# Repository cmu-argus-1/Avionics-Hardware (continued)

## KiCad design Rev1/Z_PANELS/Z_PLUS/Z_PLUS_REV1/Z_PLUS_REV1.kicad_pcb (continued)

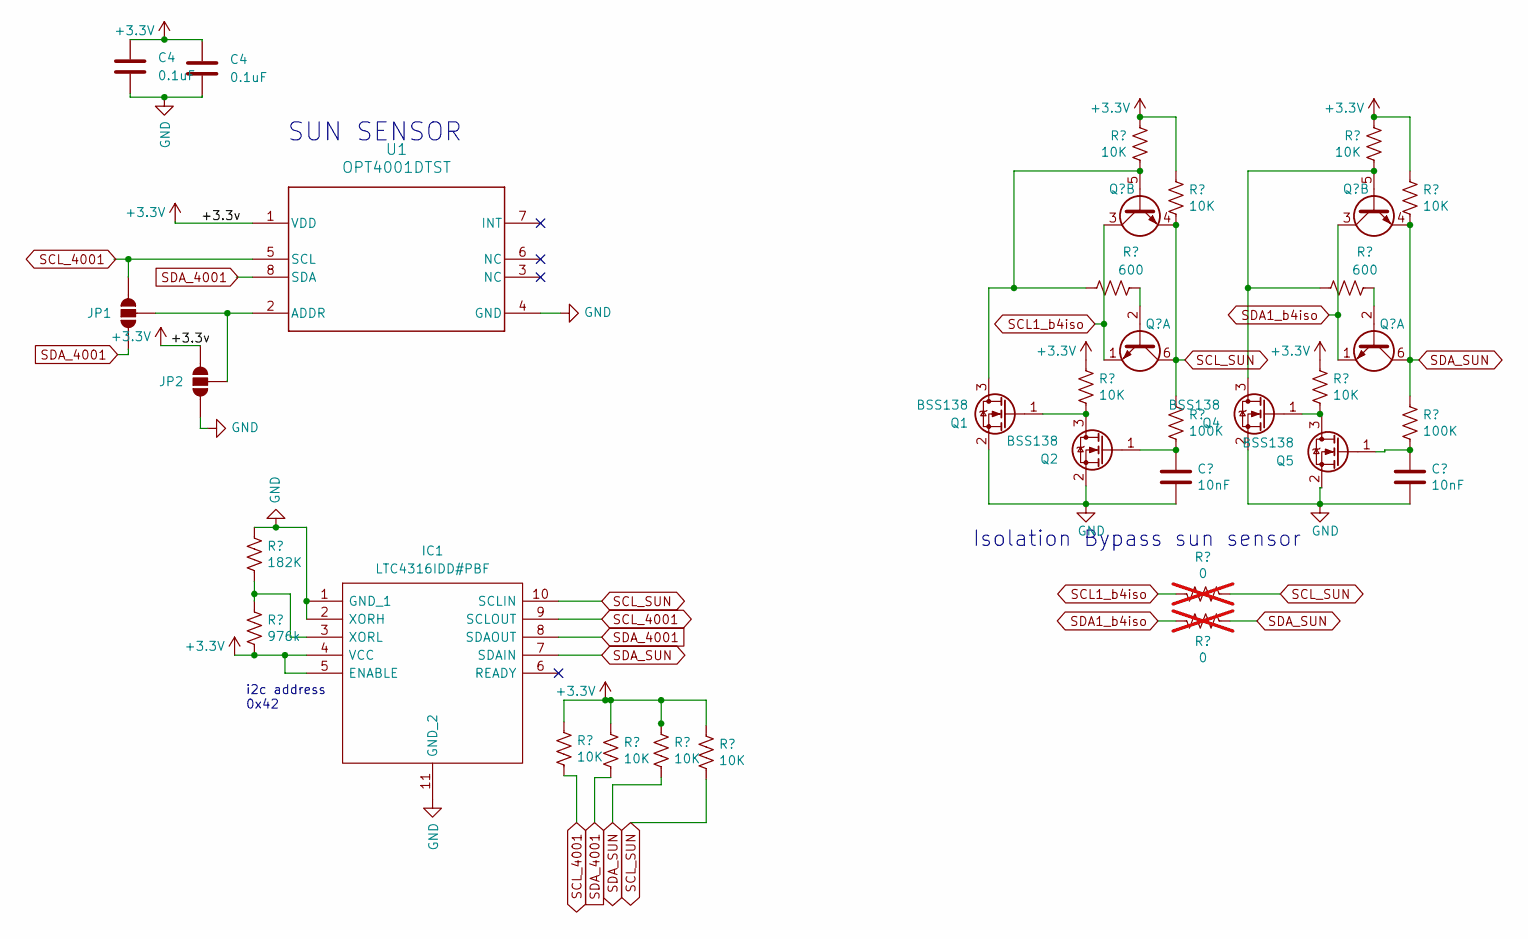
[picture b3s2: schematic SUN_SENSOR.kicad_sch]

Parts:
C3: 10nF; C_0603_1608Metric
C4: 0.1uF; C_0805_2012Metric
IC1: LTC4316IDD#PBF; SON50P300X300X85-11N-D; Manufacturer_Part_Number LTC4316IDD#PBF; Mouser Part Number 584-LTC4316IDD#PBF
JP1, JP2: SMT-JUMPER_3_NO_NO-SILK
Q1, Q2, Q4, Q5: BSS138; SOT-23
Q3, Q6: MBT2222ADW1T1; SOT-363_SC-70-6
R1: 182K; R_0805_2012Metric
R2: 976k; R_0805_2012Metric
R3, R4, R5, R6, R7, R9, R10, R14, R16, R17: 10K; R_0805_2012Metric
R8, R15: 600; R_0805_2012Metric
R11, R18: 100K; R_0805_2012Metric
R12, R13: 0; R_0603_1608Metric; not fitted
U1: OPT4001DTST; DTS0008A-MFG

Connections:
GND: C3.2, C4.2, IC1.1 (GND_1), IC1.2 (XORH), IC1.11 (GND_2), JP2.1 (A), Q1.2 (S), Q2.2 (S), Q4.2 (S), Q5.2 (S), R1.2, U1.4 (GND); also elsewhere on the board
unnamed: IC1.3 (XORL), R1.1, R2.2
unnamed: JP1.2 (C), JP2.2 (C), U1.2 (ADDR)
unnamed: Q1.3 (D), Q3.5 (B2), R8.1, R9.2
unnamed: Q1.1 (G), Q2.3 (D), R7.1
unnamed: C3.1, Q2.1 (G), R11.1
unnamed: Q3.2 (B1), R8.2
unnamed: Q4.3 (D), Q6.5 (B2), R15.2, R16.2
unnamed: Q4.1 (G), Q5.3 (D), R14.1
unnamed: Q6.2 (B1), R15.1
SCL1_b4iso: Q3.1 (E1), Q3.3 (C2), R12.1; also elsewhere on the board
SCL_4001: IC1.9 (SCLOUT), JP1.3 (B), R3.1, U1.5 (SCL); also elsewhere on the board
SCL_SUN: IC1.10 (SCLIN), Q3.4 (E2), Q3.6 (C1), R6.1, R10.1, R11.2, R12.2
SDA1_b4iso: Q6.1 (E1), Q6.3 (C2), R13.1; also elsewhere on the board
SDA_4001: IC1.8 (SDAOUT), JP1.1 (A), R4.1, U1.8 (SDA); also elsewhere on the board
SDA_SUN: IC1.7 (SDAIN), Q6.4 (E2), Q6.6 (C1), R5.1, R13.2, R17.1, R18.2

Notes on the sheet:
Isolation Bypass sun sensor
SUN SENSOR
i2c address 0x42

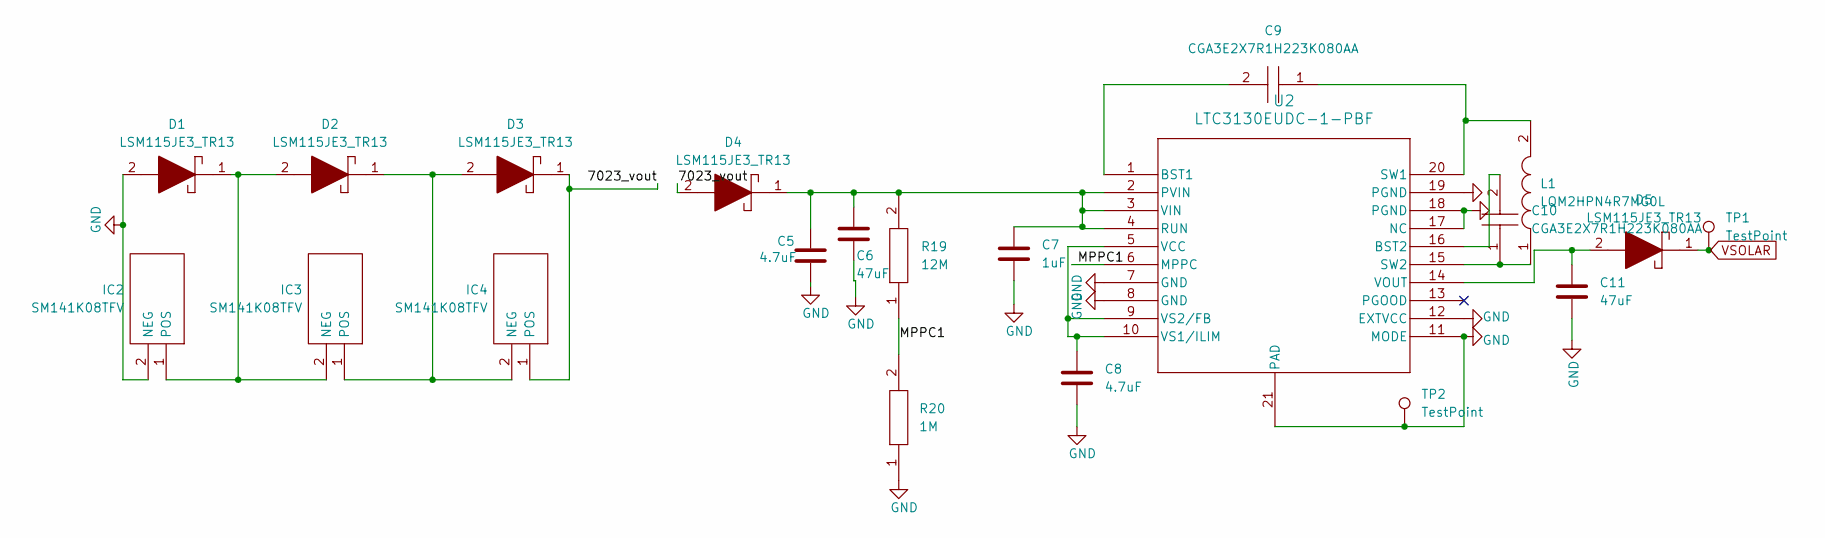
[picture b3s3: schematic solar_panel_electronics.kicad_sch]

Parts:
C5, C8: 4.7uF; C_0805_2012Metric
C6, C11: 47uF; C_0805_2012Metric
C7: 1uF; C_0805_2012Metric
C9, C10: CGA3E2X7R1H223K080AA; CAPC1608X90N; Manufacturer_Part_Number CGA3E2X7R1H223K080AA; Mouser Part Number 810-CGA3E2X7R1H223K
D1, D2, D3, D4, D5: LSM115JE3_TR13; DIOM5436X330N; Manufacturer_Part_Number LSM115JE3/TR13; Mouser Part Number 494-LSM115JE3/TR13
IC2, IC3, IC4: SM141K08TFV; SODFL520290X120N; Manufacturer_Part_Number SM141K08TFV
L1: LQM2HPN4R7MG0L; LQM2HPN1R0MG0L; Manufacturer_Part_Number LQM2HPN4R7MG0L; Mouser Part Number 81-LQM2HPN4R7MG0L
R19: 12M; RESC5025X70N; Manufacturer_Part_Number CHV2010-FX-1005ELF; Mouser Part Number 652-CHV2010FX1005ELF
R20: 1M; RESC3116X65N; Manufacturer_Part_Number RC1206FR-072M49L; Mouser Part Number 603-RC1206FR-072M49L
TP1, TP2: TestPoint; TestPoint_Loop_D1.80mm_Drill1.0mm_Beaded
U2: LTC3130EUDC-1-PBF; UDC_20_ADI

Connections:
/SOLAR_PANEL_ELECTRONICS/7023_vout: D3.1, D4.2, IC4.1 (POS)
/SOLAR_PANEL_ELECTRONICS/MPPC1: R19.1, R20.2, U2.6 (MPPC)
GND: C5.2, C6.2, C7.2, C8.2, C11.2, D1.2, IC2.2 (NEG), R20.1, TP2.1, U2.7 (GND), U2.8 (GND), U2.11 (MODE), U2.12 (EXTVCC), U2.17 (NC), U2.18 (PGND), U2.19 (PGND), U2.21 (PAD); also elsewhere on the board
unnamed: D1.1, D2.2, IC2.1 (POS), IC3.2 (NEG)
unnamed: D2.1, D3.2, IC3.1 (POS), IC4.2 (NEG)
unnamed: C9.2, U2.1 (BST1)
unnamed: C10.2, U2.16 (BST2)
unnamed: C5.1, C6.1, C7.1, D4.1, R19.2, U2.2 (PVIN), U2.3 (VIN), U2.4 (RUN)
unnamed: C9.1, L1.2, U2.20 (SW1)
unnamed: C10.1, L1.1, U2.15 (SW2)
unnamed: C8.1, U2.5 (VCC), U2.9 (VS2/FB), U2.10 (VS1/ILIM)
unnamed: C11.1, D5.2, U2.14 (VOUT)
VSOLAR: D5.1, TP1.1; also elsewhere on the board

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
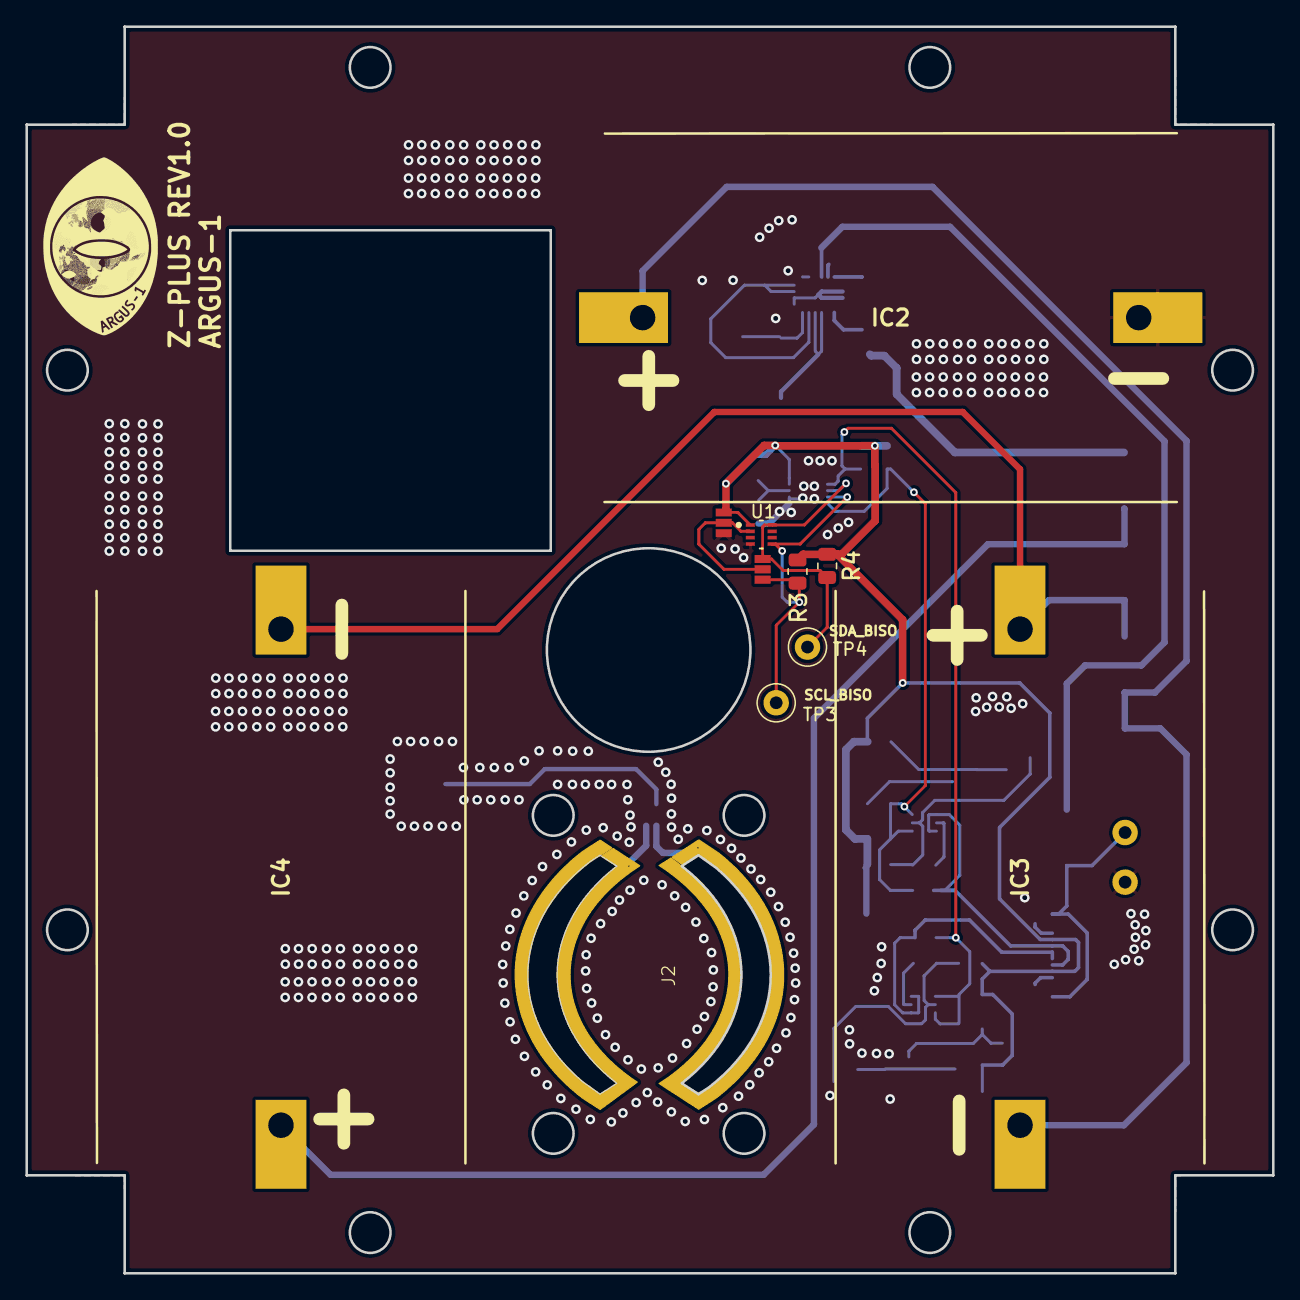
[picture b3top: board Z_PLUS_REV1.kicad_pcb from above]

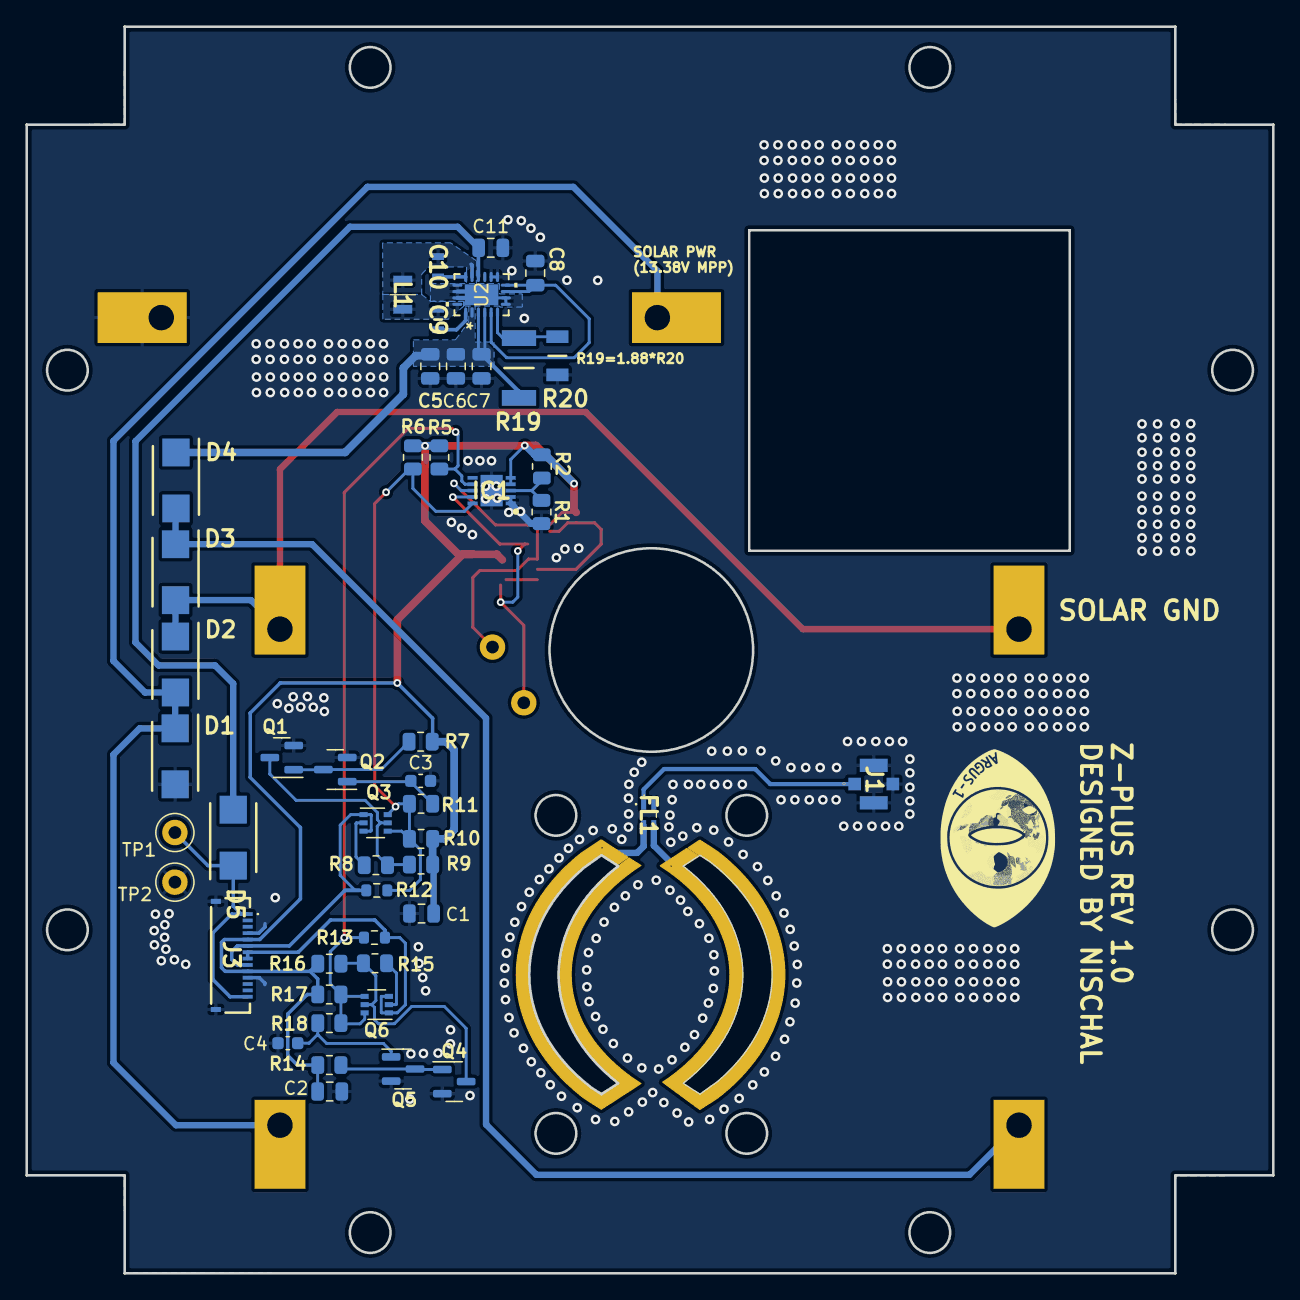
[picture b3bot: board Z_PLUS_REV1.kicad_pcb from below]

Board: 2 copper layers, 98.0 x 98.0 mm, 61 parts (49 on the bottom side), 33 nets.

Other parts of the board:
., .#2: .; ARGUS_LOGO
C1, C2: 0.1uF; C_0805_2012Metric
TP3, TP4: TestPoint; TestPoint_Loop_D1.80mm_Drill1.0mm_Beaded

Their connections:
GND: C1.2, C2.2; also elsewhere on the board
SCL_4001: TP3.1; also elsewhere on the board
SDA_4001: TP4.1; also elsewhere on the board

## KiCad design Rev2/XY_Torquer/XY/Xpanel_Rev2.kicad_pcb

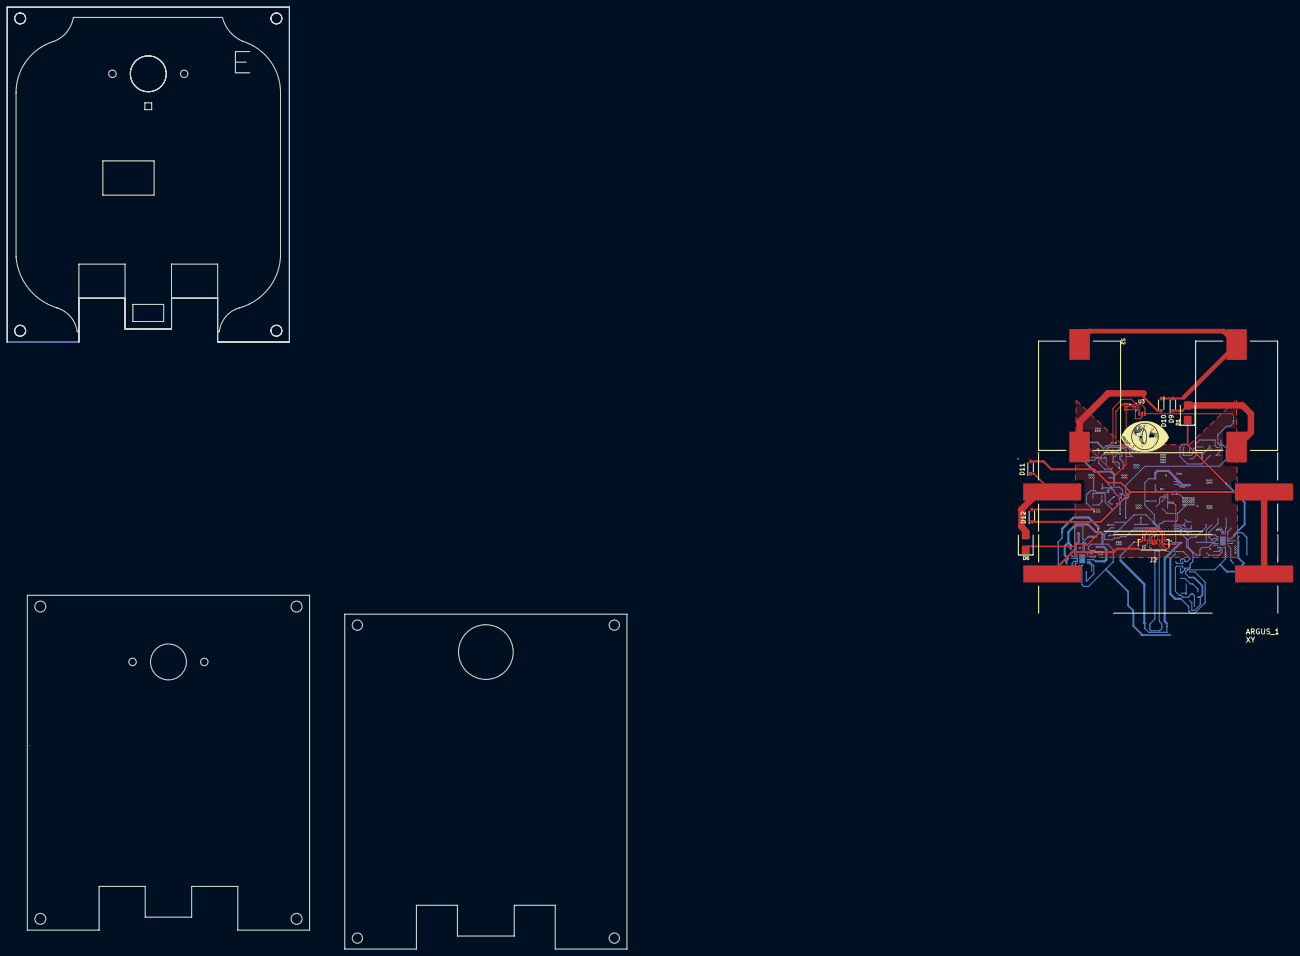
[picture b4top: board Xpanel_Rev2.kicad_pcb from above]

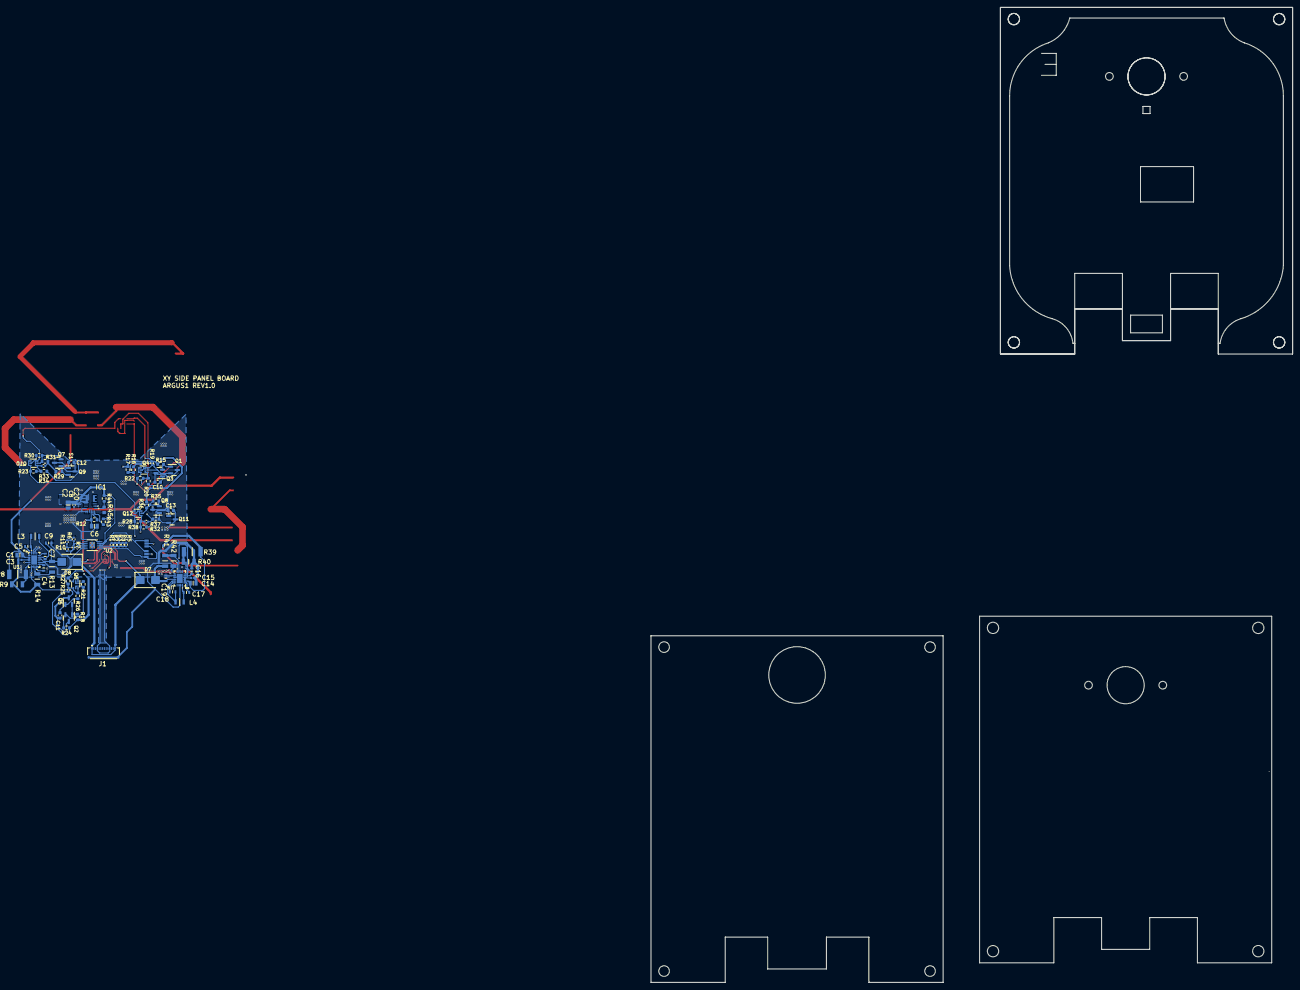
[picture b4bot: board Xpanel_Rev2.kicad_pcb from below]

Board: 4 copper layers, 103 parts (88 on the bottom side), 61 nets.

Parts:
.: .; Argus LOGO
C1, C14: CL21A476MQYNNNE; CAPC2012X135N
C2, C6: CL21A106KOQNNNE; CAPC2012X140N
C3, C15: CL05A105KQ5NNNC; CAPC1005X55N
C4, C9, C16, C19: CL10A475KQ8NNNC; CAPC1608X90N
C5, C7, C17, C18: CGA3E2X7R1H223K080AA; CAPC1608X90N
C8: 0.1uF; C_0402_1005Metric
C10, C11, C12, C13: 10nF; C_0603_1608Metric
C20: GRM033R60J224KE15D; CAPC0603X33N
D1, D6, D7, D8: B220; D_SMB
D9, D10, D11, D12: MBR0540-TP; SOD3716X135N
IC1: MPM3610AGQV-Z; MPM3610AGQVZ
J1, J2: F3311A7H121014E200
JP1, JP2, JP3, JP4: SMT-JUMPER_3_NO_NO-SILK
L3, L4: LQM2HPN4R7MG0L; LQM2HPN1R0MG0L
Q1, Q2, Q3, Q5, Q7, Q8, Q9, Q11: BSS138; SOT-23
Q4, Q6, Q10, Q12: MBT2222ADW1T1; SOT-363_SC-70-6
R1, R2, R3, R4, R5, R6, R7, R10, R11: 0; R_0402_1005Metric
R8, R39: CHV2010-FX-1005ELF; RESC5025X70N
R9, R14, R42: RC1206FR-072ML; RESC3116X65N
R12, R20, R26, R34, R38, R43, R44: 100K; R_0603_1608Metric
R13, R41: RV1206JR-0722ML; RESC3116X65N
R15, R17, R18, R24, R29, R31, R32, R36: 10K; R_0603_1608Metric
R16, R21, R30, R35: 600; R_0603_1608Metric
R19, R25, R33, R37: 10K; R_0402_1005Metric
R22, R23, R27, R28: 0; R_0603_1608Metric
R40: RC1206FR-072M49L; RESC3116X65N
R45: RMCF0603FT19K1; RESC1608X55N
S1, S2: sol_pan_32x24; solar_panel_SM500K12TF_32x24
S3, S4: sol_pan_70x23; sol_pan_SM141K10TFS_70x23
U1, U4: LTC3130EUDC-1-PBF; UDC_20_ADI
U2: DRV8830DGQ; IC_XTR111AIDGQR
U3: OPT4001DTST; DTS0008A-MFG

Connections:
5V: C2.2, C8.1, C20.1, IC1.7 (OUT_1), IC1.8 (OUT_2), IC1.9 (OUT_3), IC1.22 (OUT_4), R44.1, U2.4 (VCC)
+3.3V: J2.5, J2.10, JP2.3 (B), R7.2, R10.2, R15.2, R17.1, R18.2, R19.2, R24.1, R25.2, R29.2, R31.1, R32.2, R33.2, R36.1, R37.2, U3.1 (VDD)
/TORQUE_COIL/nc: IC1.4 (SW_1), IC1.5 (SW_2), IC1.6 (SW_3), IC1.21 (SW_4)
/solar_panel_electronics/3224_vout: D1.2 (A), D9.1, S1.1 (Pos)
/solar_panel_electronics/7023_vout: D6.2 (A), D11.1, S3.1 (Pos)
/solar_panel_electronics/FB: R13.1, R14.2, U1.9 (VS2/FB)
/solar_panel_electronics/FB1: R41.1, R42.2, U4.9 (VS2/FB)
/solar_panel_electronics/MPPC: R8.1, R9.2, U1.6 (MPPC)
/solar_panel_electronics/MPPC1: R39.1, R40.2, U4.6 (MPPC)
GND: C1.1, C2.1, C3.1, C4.1, C6.1, C8.2, C9.1, C10.2, C11.2, C12.2, C13.2, C14.1, C15.1, C16.1, C19.1, C20.2, D10.2, D12.2, IC1.3 (AGND), IC1.12 (PGND_1), IC1.13 (PGND_2), IC1.14 (PGND_3), J1.4, J1.11, J1.MP1, J1.MP2, J2.4, J2.11, J2.MP1, J2.MP2, JP2.1 (A), Q1.3 (D), Q2.3 (D), Q3.3 (D), Q5.3 (D), Q7.3 (D), Q8.3 (D), Q9.3 (D), Q11.3 (D), R1.2, R2.2, R3.2, R4.2, R5.2, R6.1, R9.1, R11.1, R14.1, R40.1, R42.1, R45.2, S2.2 (Neg), S4.2 (Neg), U1.7 (GND), U1.8 (GND), U1.11 (MODE), U1.12 (EXTVCC), U1.18 (PGND), U1.19 (PGND), U2.5 (GND), U2.11 (EP), U3.4 (GND), U4.7 (GND), U4.8 (GND), U4.11 (MODE), U4.12 (EXTVCC), U4.18 (PGND), U4.19 (PGND)
unnamed: C1.2, C3.2, D1.1 (K), R8.2, U1.2 (PVIN), U1.3 (VIN), U1.4 (RUN)
unnamed: C14.2, C15.2, D6.1 (K), R39.2, U4.2 (PVIN), U4.3 (VIN), U4.4 (RUN)
unnamed: C19.2, D7.2 (A), R41.2, U4.14 (VOUT)
unnamed: C9.2, D8.2 (A), R13.2, U1.14 (VOUT)
unnamed: IC1.17 (EN), R12.1
unnamed: IC1.1 (FB), R44.2, R45.1
unnamed: IC1.18 (PG), R43.1
unnamed: IC1.2 (VCC), R43.2
unnamed: JP1.2 (C), JP2.2 (C), U3.2 (ADDR)
unnamed: JP3.1 (A), JP4.3 (B), U2.1 (OUT2)
unnamed: JP3.3 (B), JP4.1 (A), U2.3 (OUT1)
unnamed: Q1.1 (G), Q3.2 (S), R15.1
unnamed: Q1.2 (S), Q4.5 (B2), R16.1, R17.2
unnamed: Q2.1 (G), Q5.2 (S), R18.1
unnamed: Q2.2 (S), Q6.5 (B2), R21.1, R24.2
unnamed: C10.1, Q3.1 (G), R20.1
unnamed: Q4.2 (B1), R16.2
unnamed: C11.1, Q5.1 (G), R26.1
unnamed: Q6.2 (B1), R21.2
unnamed: Q7.1 (G), Q9.2 (S), R29.1
unnamed: C12.1, Q9.1 (G), R34.1
unnamed: Q10.2 (B1), R30.1
unnamed: Q7.2 (S), Q10.5 (B2), R30.2, R31.2
unnamed: C13.1, Q11.1 (G), R38.1
unnamed: Q8.1 (G), Q11.2 (S), R32.1
unnamed: Q12.2 (B1), R35.1
unnamed: Q8.2 (S), Q12.5 (B2), R35.2, R36.2
unnamed: D9.2, D10.1, S1.2 (Neg), S2.1 (Pos)
unnamed: D11.2, D12.1, S3.2 (Neg), S4.1 (Pos)
unnamed: C5.2, U1.1 (BST1)
unnamed: C7.2, U1.16 (BST2)
unnamed: C5.1, L3.2, U1.20 (SW1)
unnamed: C7.1, L3.1, U1.15 (SW2)
unnamed: C4.2, U1.5 (VCC), U1.10 (VS1/ILIM)
unnamed: R6.2, R7.1, U2.7 (A0)
unnamed: R10.1, R11.2, U2.8 (A1)
unnamed: R1.1, R2.1, R3.1, R4.1, R5.1, U2.2 (ISENSE)
unnamed: C17.2, U4.1 (BST1)
unnamed: C18.2, U4.16 (BST2)
unnamed: C17.1, L4.2, U4.20 (SW1)
unnamed: C18.1, L4.1, U4.15 (SW2)
unnamed: C16.2, U4.5 (VCC), U4.10 (VS1/ILIM)
SCL1_b4iso: J2.6, J2.9, Q4.1 (E1), Q4.3 (C2), Q6.1 (E1), Q6.3 (C2), R22.1, R27.1
SCL_SUN: JP1.3 (B), Q4.4 (E2), Q4.6 (C1), R19.1, R20.2, R22.2, U3.5 (SCL)
SCL_TORQUE: Q6.4 (E2), Q6.6 (C1), R25.1, R26.2, R27.2, U2.10 (SCL)
SDA1_b4iso: J2.7, J2.8, Q10.1 (E1), Q10.3 (C2), Q12.1 (E1), Q12.3 (C2), R23.1, R28.1
SDA_SUN: JP1.1 (A), Q10.4 (E2), Q10.6 (C1), R23.2, R33.1, R34.2, U3.8 (SDA)
SDA_TORQUE: Q12.4 (E2), Q12.6 (C1), R28.2, R37.1, R38.2, U2.9 (SDA)
VBATT: C6.2, IC1.16 (IN), J2.2, J2.3, J2.12, J2.13, R12.2
VSOLAR: D7.1 (K), D8.1 (K), J1.1, J1.14, J2.1, J2.14
coils: JP3.2 (C), JP4.2 (C)
